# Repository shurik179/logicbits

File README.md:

# Logic Gates Demonstration Kit

This directory contains files related to my Logic Gate Demonstraiton kit. This project is described in detail in my [Instructable](https://www.instructables.com/Logic-Gates-Demonstration-Kit/).

All files are released under MIT license; see LICENSE file in this directory for details.

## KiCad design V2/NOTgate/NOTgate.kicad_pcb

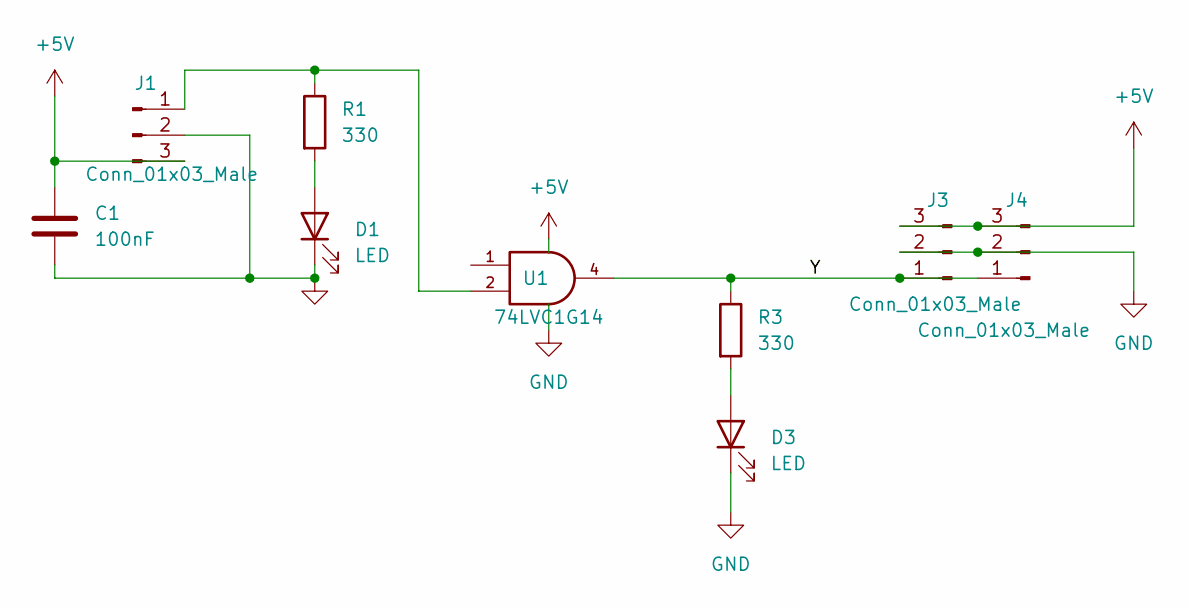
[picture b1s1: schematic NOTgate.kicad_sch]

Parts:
C1: 100nF; C_0603_1608Metric; LCSC C14663
D1, D3: LED; LITE_ON_LTST_C230TBKT-LED_1206_3216Metric_ReverseMount; LCSC C125109
J1, J3, J4: Conn_01x03_Male; Molex_PicoBlade_53261-0371_1x03-1MP_P1.25mm_Horizontal; LCSC C22075
R1, R3: 330; R_0603_1608Metric; LCSC C23138
U1: 74LVC1G14; SOT-23-5; LCSC C7835

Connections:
+5V: C1.1, J1.3, J3.3, J4.3, U1.5 (VCC)
/Y: J3.1, J4.1, R3.1, U1.4
GND: C1.2, D1.1 (K), D3.1 (K), J1.2, J3.2, J4.2, U1.3 (GND)
unnamed: D1.2 (A), R1.2
unnamed: D3.2 (A), R3.2
unnamed: J1.1, R1.1, U1.2

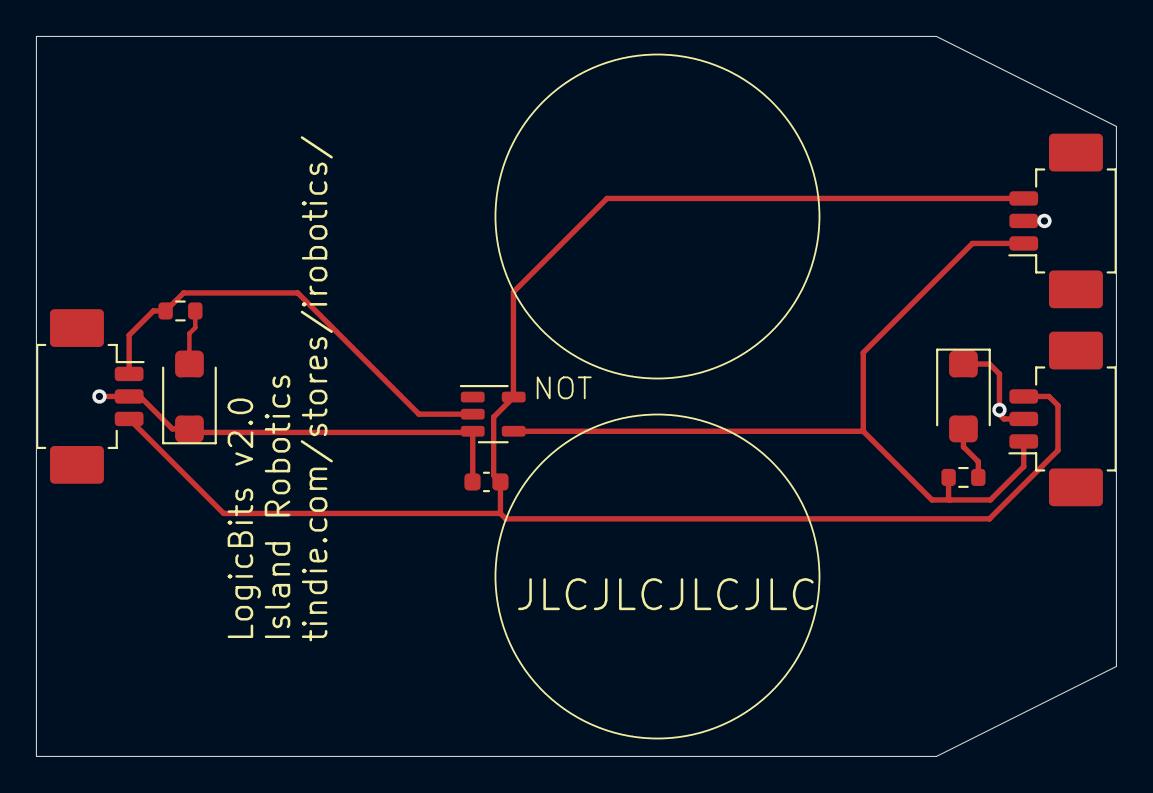
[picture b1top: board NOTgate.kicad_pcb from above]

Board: 2 copper layers, 60.0 x 40.0 mm, 9 parts (0 on the bottom side), 6 nets.

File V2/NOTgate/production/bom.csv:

Designator,Footprint,Quantity,Value,LCSC Part #
C1,0603,1,100nF,C14663
"D1, D3",LITE_ON_LTST_C230TBKT-LED_1206_3216Metric_ReverseMount,2,LED,C125109
"J1, J3, J4",Molex_PicoBlade_53261-0371_1x03-1MP_P1.25mm_Horizontal,3,Conn_01x03_Male,C22075
"R1, R3",0603,2,330,C23138
U1,SOT-23-5,1,74LVC1G14,C7835

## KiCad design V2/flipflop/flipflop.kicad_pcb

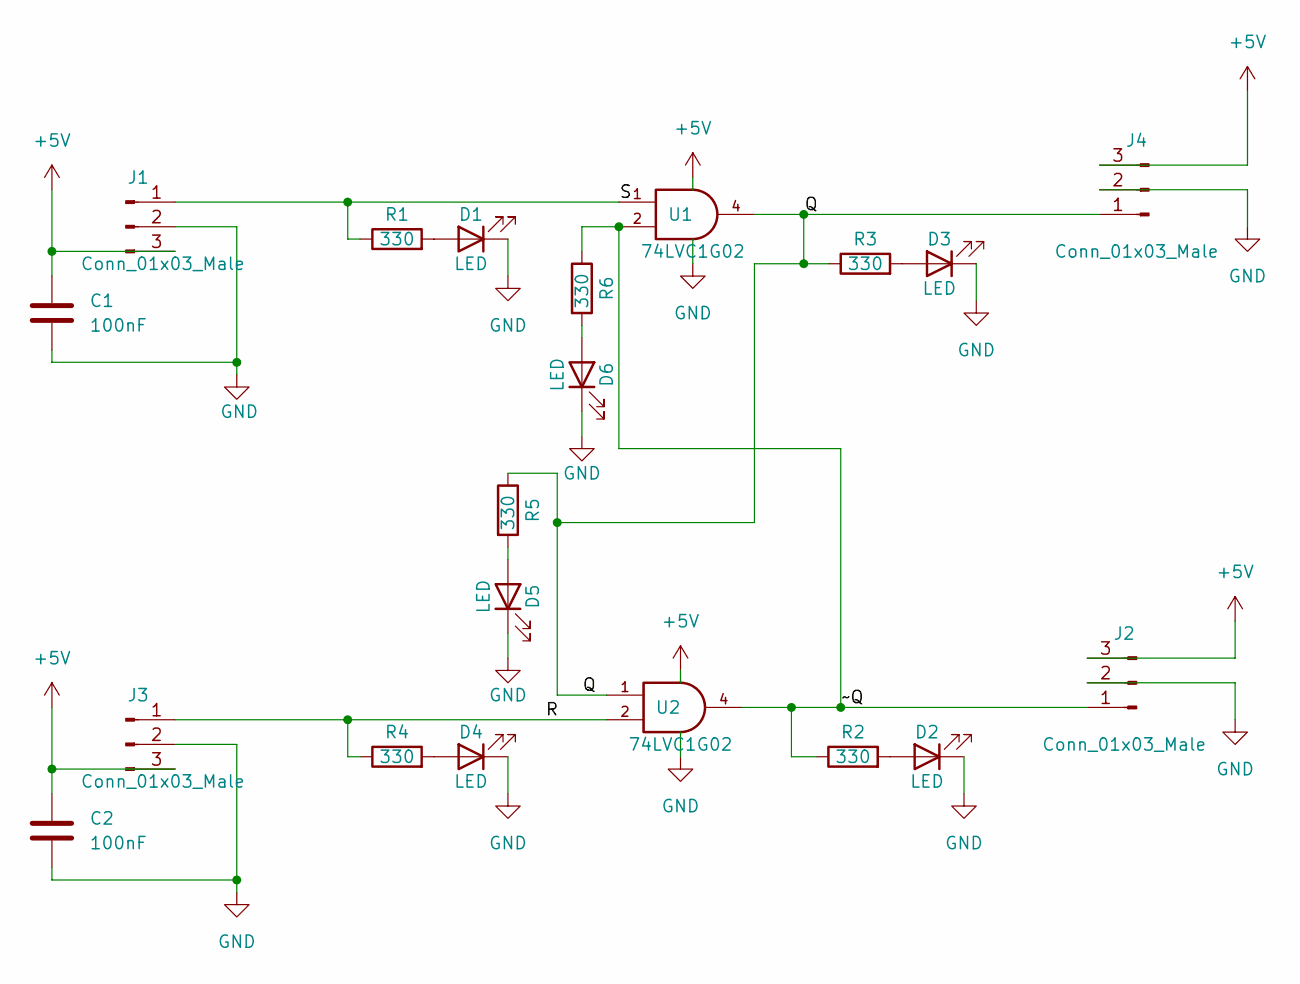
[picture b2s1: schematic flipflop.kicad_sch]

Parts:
C1, C2: 100nF; C_0603_1608Metric; LCSC C14663
D1, D2, D3, D4, D5, D6: LED; LITE_ON_LTST_C230TBKT-LED_1206_3216Metric_ReverseMount; LCSC C125109
J1, J2, J3, J4: Conn_01x03_Male; Molex_PicoBlade_53261-0371_1x03-1MP_P1.25mm_Horizontal; LCSC C22075
R1, R2, R3, R4, R5, R6: 330; R_0603_1608Metric; LCSC C23138
U1, U2: 74LVC1G02; SOT-23-5; LCSC C16360

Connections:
+5V: C1.1, C2.1, J1.3, J2.3, J3.3, J4.3, U1.5 (VCC), U2.5 (VCC)
/Q: J4.1, R3.1, R5.1, U1.4, U2.1
/R: J3.1, R4.1, U2.2
/S: J1.1, R1.1, U1.1
/~Q: J2.1, R2.1, R6.1, U1.2, U2.4
GND: C1.2, C2.2, D1.1 (K), D2.1 (K), D3.1 (K), D4.1 (K), D5.1 (K), D6.1 (K), J1.2, J2.2, J3.2, J4.2, U1.3 (GND), U2.3 (GND)
unnamed: D1.2 (A), R1.2
unnamed: D2.2 (A), R2.2
unnamed: D3.2 (A), R3.2
unnamed: D4.2 (A), R4.2
unnamed: D5.2 (A), R5.2
unnamed: D6.2 (A), R6.2

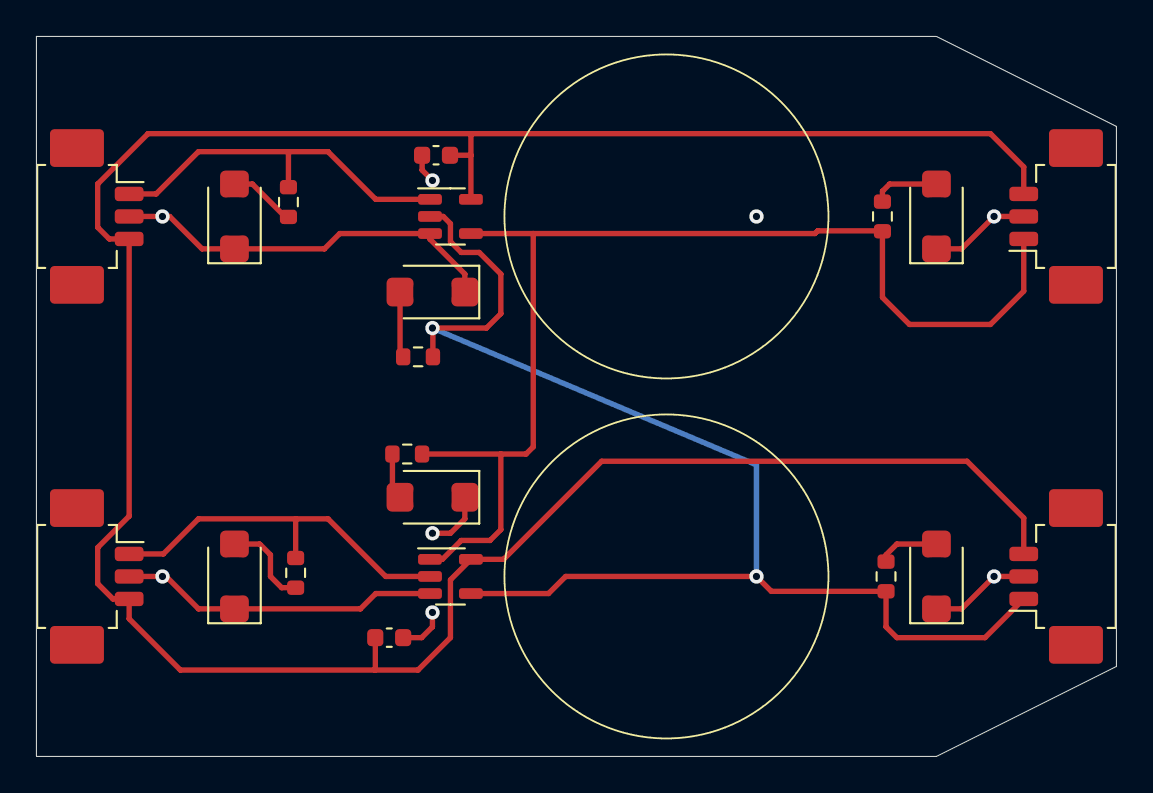
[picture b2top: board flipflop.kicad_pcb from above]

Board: 2 copper layers, 60.0 x 40.0 mm, 20 parts (0 on the bottom side), 12 nets.

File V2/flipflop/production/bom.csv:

Designator,Footprint,Quantity,Value,LCSC Part #
"C1, C2",0603,2,100nF,C14663
"D1, D2, D3, D4, D5, D6",LITE_ON_LTST_C230TBKT-LED_1206_3216Metric_ReverseMount,6,LED,C125109
"J1, J2, J3, J4",Molex_PicoBlade_53261-0371_1x03-1MP_P1.25mm_Horizontal,4,Conn_01x03_Male,C22075
"R1, R2, R3, R4, R5, R6",0603,6,330,C23138
"U1, U2",SOT-23-5,2,74LVC1G02,C16360

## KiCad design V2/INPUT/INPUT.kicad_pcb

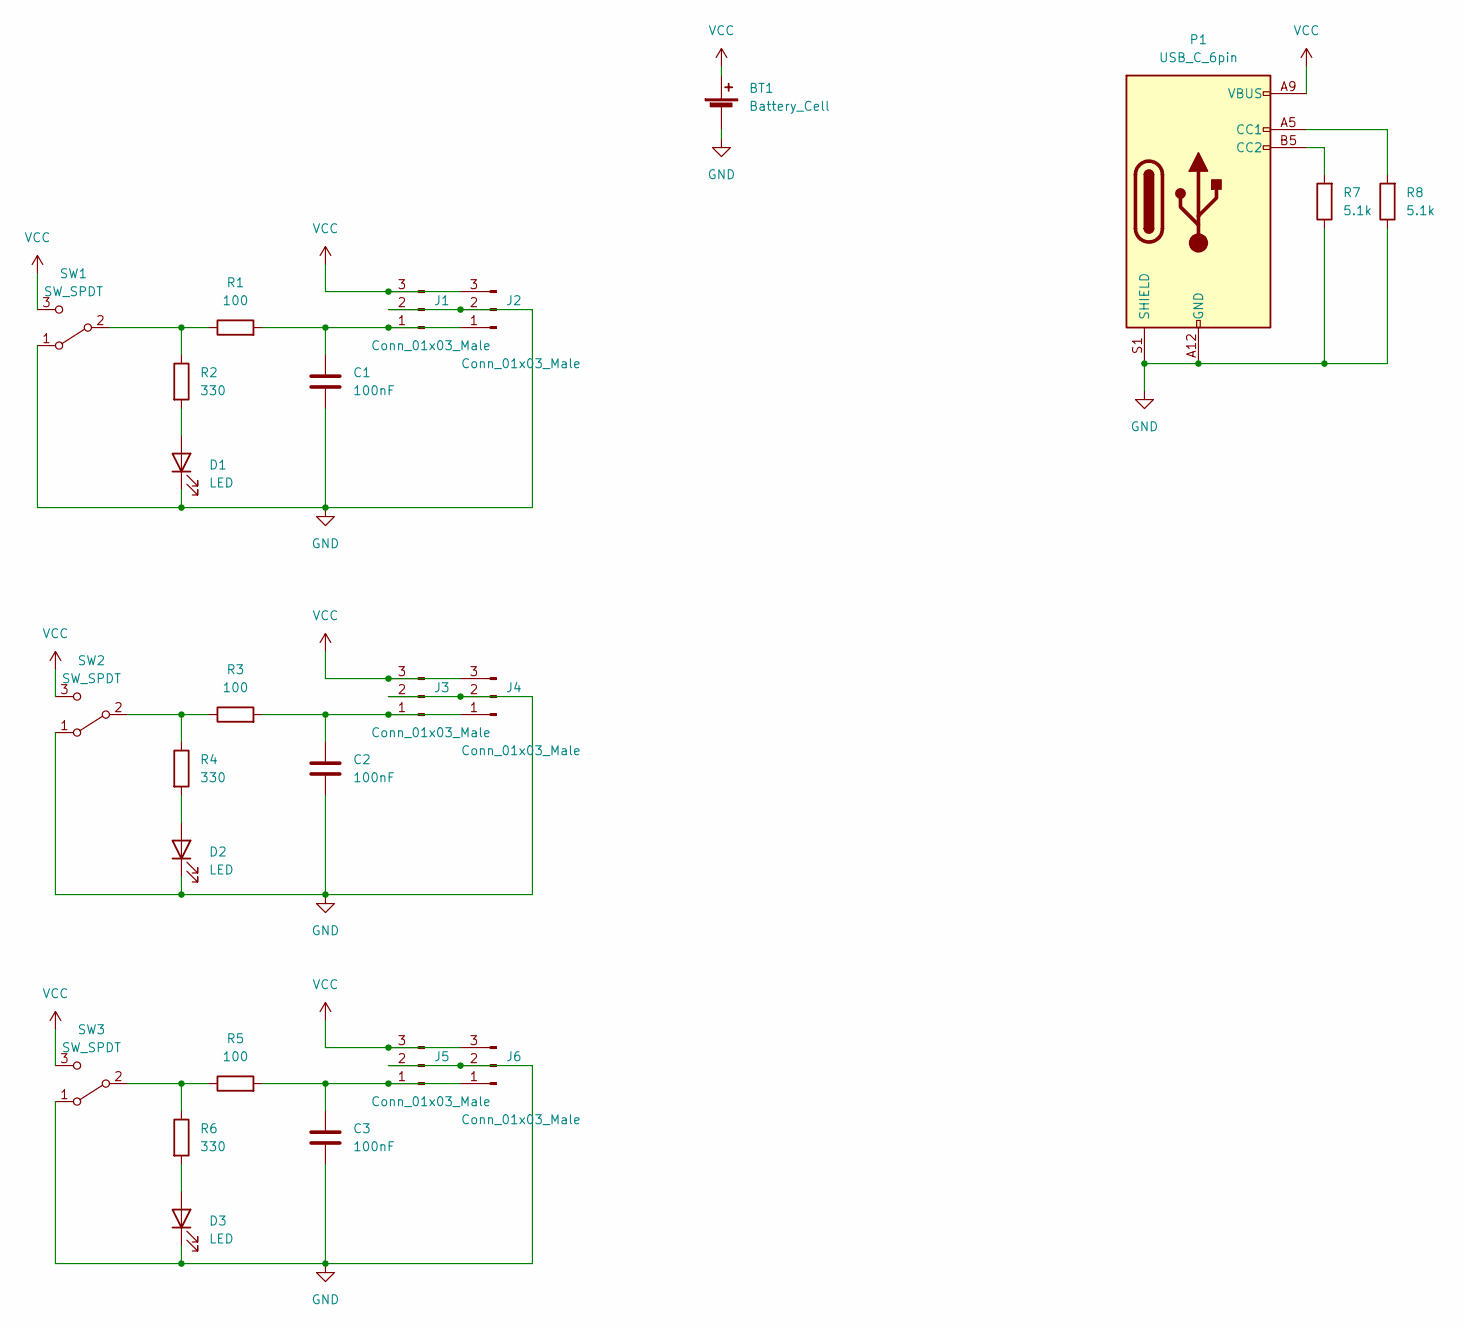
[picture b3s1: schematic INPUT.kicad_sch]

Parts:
BT1: Battery_Cell; BatteryHolder_QJ_BS6-CR2032; LCSC C70377
C1, C2, C3: 100nF; C_0603_1608Metric; LCSC C14663
D1, D2, D3: LED; LITE_ON_LTST_C230TBKT-LED_1206_3216Metric_ReverseMount; LCSC C125109
J1, J2, J3, J4, J5, J6: Conn_01x03_Male; Molex_PicoBlade_53261-0371_1x03-1MP_P1.25mm_Horizontal; LCSC C22075
P1: USB_C_6pin; USB_C_Receptacle_Korean_Hroparts-31-M-17; LCSC C283540
R1, R3, R5: 100; R_0603_1608Metric; LCSC C22775
R2, R4, R6: 330; R_0603_1608Metric; LCSC C23138
R7, R8: 5.1k; R_0603_1608Metric; LCSC C23186
SW1, SW2, SW3: SW_SPDT; SW_SPDT_MK_12C02; LCSC C963206

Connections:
GND: BT1.2 (-), C1.2, C2.2, C3.2, D1.1 (K), D2.1 (K), D3.1 (K), J1.2, J2.2, J3.2, J4.2, J5.2, J6.2, P1.A12 (GND), P1.B12 (GND), P1.S1 (SHIELD), R7.1, R8.1, SW1.1 (A), SW2.1 (A), SW3.1 (A)
unnamed: D1.2 (A), R2.2
unnamed: D2.2 (A), R4.2
unnamed: D3.2 (A), R6.2
unnamed: C1.1, J1.1, J2.1, R1.2
unnamed: C2.1, J3.1, J4.1, R3.2
unnamed: C3.1, J5.1, J6.1, R5.2
unnamed: P1.A5 (CC1), R8.2
unnamed: P1.B5 (CC2), R7.2
unnamed: R1.1, R2.1, SW1.2 (B)
unnamed: R3.1, R4.1, SW2.2 (B)
unnamed: R5.1, R6.1, SW3.2 (B)
VCC: BT1.1 (+), J1.3, J2.3, J3.3, J4.3, J5.3, J6.3, P1.A9 (VBUS), P1.B9 (VBUS), SW1.3 (C), SW2.3 (C), SW3.3 (C)

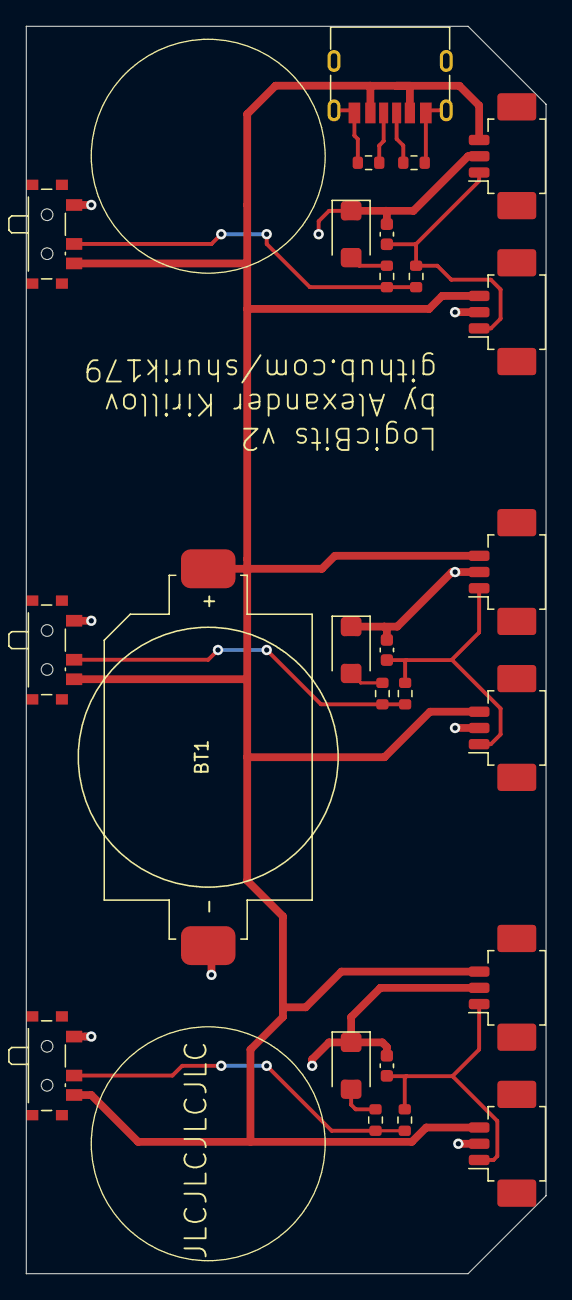
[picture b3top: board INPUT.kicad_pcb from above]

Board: 2 copper layers, 40.0 x 96.0 mm, 25 parts (0 on the bottom side), 13 nets.

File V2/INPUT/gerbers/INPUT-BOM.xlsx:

Designator | Footprint | Comment | JLCPCB Part #（optional）
R5,R3,R1 | R_0603_1608Metric | 100 | C22775
D1,D3,D2 | LITE_ON_LTST_C230TBKT-LED_1206_3216Metric_ReverseMount | LED - blue | C125109
BT1 | BatteryHolder_QJ_BS6-CR2032 | Battery_Cell | C70377
J4,J6,J3,J1,J2,J5 | Molex_PicoBlade_53261-0371_1x03-1MP_P1.25mm_Horizontal | Conn_01x03_Male | C22075
R6,R4,R2 | R_0603_1608Metric | 330 | C23138
C1,C3,C2 | C_0603_1608Metric | 100nF | C14663
R8,R7 | R_0603_1608Metric | 5.1k | C23186
P1 | USB_C_Receptacle_Korean_Hroparts-31-M-17 | USB_C_6pin | C2764612

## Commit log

2021-01-13 Initial upload
2021-01-13 updated input panel
2021-01-18 updated for v1.3
2021-01-19 Updating README
2021-01-19 Fixing image link
2025-05-10 updating for v2.0
2025-05-12 reorganization
